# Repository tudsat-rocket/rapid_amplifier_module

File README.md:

# FRoDo Amplifier Module
this module is meant to be a general-purpose amplifier which is going to be used for all analogue sensors which will be in the rocket, those include the WIKA pressure sensors as well as the fancy-fins strain gauges.

## Description
The main function of the module is to amplify signals with low voltage levels that are too small to be useful for our ADCs. Therefore the board has two sides with solder pads, one to connect to the IO board and one to connect to a sensor. The layout is designed in a way, that the sensor side is compatible with the WIKA TPR-Flex PCBs.

## Features
* Selectable gain (1-1000) -> the selection of RG1 will determine the gain (G = 1 + 49,4kOhm/RG)
* selectable offset -> output offset can either be 0V or Vcc/2
* Breakaway mounting holes
## Connections
### To IO-Board:
Connects the amplifier module with the IO-Board with the following pins:
* u+  ->  positive supply voltage (3-36V)
* u-  ->  gnd as "neg" supply voltage (only use in single supply mode) | reference for the output signal.
* o+  ->  amplified signal, references gnd (u-)
* ref  ->  selected reference signal (0V or Vcc/2) can be used to get additional information (e.g. detect noise on supply line(?))

### To sensor:
Connects the amplifier module with the Sensor with the following pins:
* u+  -> positive supply voltage (filtered supply voltage)
* u-  -> neg. supply voltage (gnd)
* s+  -> positive signal
* s-  -> negative signal

## User guideline:
The Gain resistor (RG1) must be chosen in a way that the expected maximum amplified voltage is lower than 4.85V (5V - 0.15V) and the expected minimum amplified voltage is higher than 0.1V if a smaller (or negative) output voltage is expected the solder jumper for the reference voltage needs to be connected to 3 to set an output shift.
Only if the connected sensor is expected to output a signal which exclusively results in an output signal that is in the above given values, can the reference solder jumper be set to 1.

The above-given adjustments are necessary as the IO module is only able to read values between 0V and 5V. A higher Input voltage can be used if the connected sensor needs a supply voltage which exceeds 5V. The amplified signal then still needs to be smaller than the given 4.85V.

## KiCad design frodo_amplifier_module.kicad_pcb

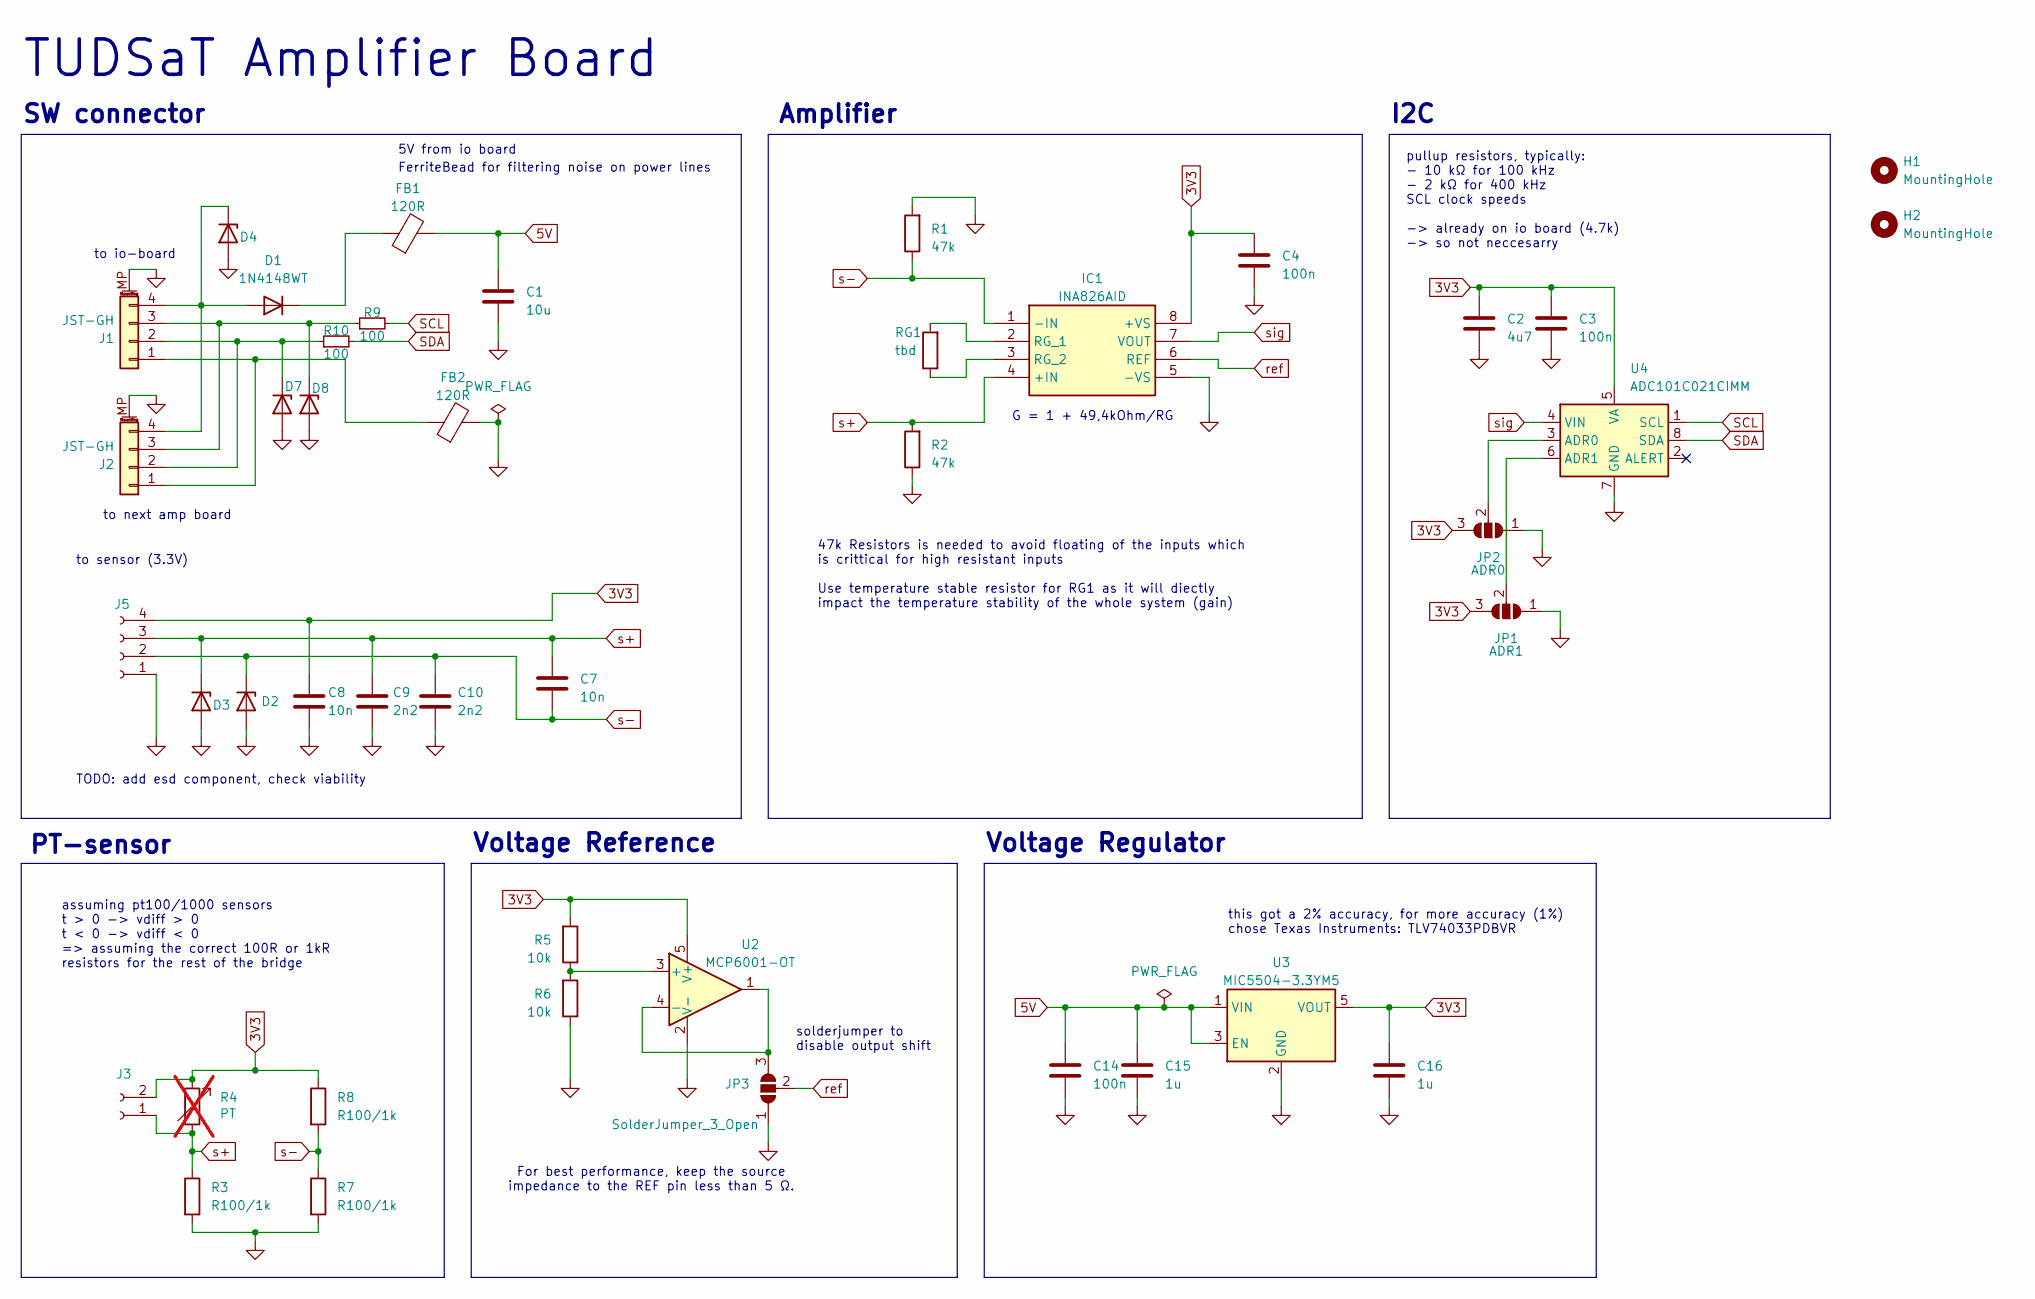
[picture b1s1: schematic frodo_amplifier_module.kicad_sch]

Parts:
C1: 10u; C_0402_1005Metric; LCSC C315248
C2: 4u7; C_0402_1005Metric; LCSC C23733
C3, C4, C14: 100n; C_0402_1005Metric; LCSC C1525
C7, C8: 10n; C_0402_1005Metric; LCSC C15195
C9, C10: 2n2; C_0402_1005Metric; LCSC C84703
C15, C16: 1u; C_0402_1005Metric; LCSC C76999
D1: 1N4148WT; D_SOD-523
D2, D3, D4, D7, D8: ESD5Zxx; D_SOD-523
FB1, FB2: 120R; L_0402_1005Metric; LCSC C76891
H1, H2: MountingHole; MountingHole_2.2mm_M2_DIN965_Pad
IC1: INA826AID; WSON-8-1EP_3x3mm_P0.5mm_EP1.2x2mm; Mouser Part Number 595-INA826AID
J1, J2: JST-GH; JST_GH_SM04B-GHS-TB_1x04-1MP_P1.25mm_Horizontal; Part# BM04B-GHS-TBT; LCSC C161692
J3: Conn_01x02_Socket; R_Axial_DIN0204_L3.6mm_D1.6mm_P1.90mm_Vertical
J5: Conn_01x04_Socket; PinHeader_1x04_P1.27mm_Vertical
JP1: ADR1; SolderJumper-3_P1.3mm_Open_RoundedPad1.0x1.5mm
JP2: ADR0; SolderJumper-3_P1.3mm_Open_RoundedPad1.0x1.5mm
JP3: SolderJumper_3_Open; SolderJumper-3_P1.3mm_Open_Pad1.0x1.5mm
R1: 47k; R_0402_1005Metric; LCSC C25792
R2: 47k; R_0402_1005Metric_Pad0.72x0.64mm_HandSolder; LCSC C25792
R3, R7, R8: R100/1k; R_0805_2012Metric_Pad1.20x1.40mm_HandSolder
R4: PT; not fitted
R5, R6: 10k; R_0402_1005Metric_Pad0.72x0.64mm_HandSolder; LCSC C25744
R9, R10: 100; R_0402_1005Metric; Part# RC0402FR-07100RL; LCSC# C106232
RG1: tbd; R_1206_3216Metric_Pad1.30x1.75mm_HandSolder
U2: MCP6001-OT; SOT-23-5; LCSC C116490
U3: MIC5504-3.3YM5; SOT-23-5; LCSC C3021093
U4: ADC101C021CIMM; MSOP-8_3x3mm_P0.65mm; LCSC C1543337

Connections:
3V3: C2.1, C3.1, C4.1, C8.1, C16.1, IC1.8 (+VS), J3.2, J5.4, JP1.3 (B), JP2.3 (B), R4.1, R5.2, R8.1, U2.5 (V+), U3.5 (VOUT), U4.5 (VA)
5V: C1.1, C14.1, C15.1, FB1.2, U3.1 (VIN), U3.3 (EN)
GND: C1.2, C2.2, C3.2, C4.2, C8.2, C9.2, C10.2, C14.2, C15.2, C16.2, D2.2 (A), D3.2 (A), D4.2 (A), D7.2 (A), D8.2 (A), FB2.2, IC1.5 (-VS), J1.MP (MountPin), J2.MP (MountPin), J5.1, JP1.1 (A), JP2.1 (A), JP3.1 (A), R1.2, R2.1, R3.2, R6.1, R7.2, U2.2 (V-), U3.2 (GND), U4.7 (GND)
unnamed: D1.2 (A), D4.1 (K), J1.4, J2.4
unnamed: D1.1 (K), FB1.1
unnamed: D7.1 (K), J1.2, J2.2, R10.1
unnamed: D8.1 (K), J1.3, J2.3, R9.1
unnamed: IC1.2 (RG_1), RG1.2
unnamed: IC1.3 (RG_2), RG1.1
unnamed: FB2.1, J1.1, J2.1
unnamed: JP1.2 (C), U4.6 (ADR1)
unnamed: JP2.2 (C), U4.3 (ADR0)
unnamed: JP3.3 (B), U2.1, U2.4 (-)
unnamed: R5.1, R6.2, U2.3 (+)
SCL: R9.2, U4.1 (SCL)
SDA: R10.2, U4.8 (SDA)
ref: IC1.6 (REF), JP3.2 (C)
s+: C7.1, C9.1, D3.1 (K), IC1.4 (+IN), J3.1, J5.3, R2.2, R3.1, R4.2
s-: C7.2, C10.1, D2.1 (K), IC1.1 (-IN), J5.2, R1.1, R7.1, R8.2
sig: IC1.7 (VOUT), U4.4 (VIN)

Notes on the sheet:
pullup resistors, typically: - 10 kΩ for 100 kHz - 2 kΩ for 400 kHz SCL clock speeds -> already on io board (4.7k) -> so not neccesarry
to sensor (3.3V)
G = 1 + 49,4kOhm/RG
SW connector
Voltage Regulator
to next amp board
TODO: add esd component, check viability
5V from io board
FerriteBead for filtering noise on power lines
solderjumper to disable output shift
TUDSaT Amplifier Board
Voltage Reference
47k Resistors is needed to avoid floating of the inputs which is crittical for high resistant inputs Use temperature stable resistor for RG1 as it will diectly impact the temperature stability of the whole system (gain)
I2C
assuming pt100/1000 sensors t > 0 -> vdiff > 0 t < 0 -> vdiff < 0 => assuming the correct 100R or 1kR resistors for the rest of the bridge
Amplifier
PT-sensor
this got a 2% accuracy, for more accuracy (1%) chose Texas Instruments: TLV74033PDBVR
to io-board
For best performance, keep the source impedance to the REF pin less than 5 Ω.

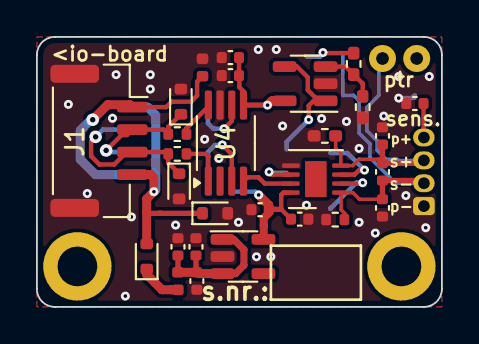
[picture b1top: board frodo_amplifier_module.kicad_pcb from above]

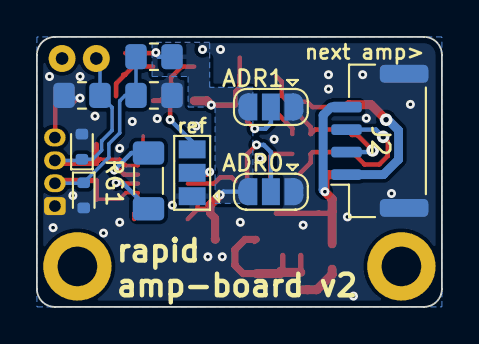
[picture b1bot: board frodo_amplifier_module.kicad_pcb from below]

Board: 4 copper layers, 22.5 x 15.0 mm, 42 parts (10 on the bottom side), 20 nets.

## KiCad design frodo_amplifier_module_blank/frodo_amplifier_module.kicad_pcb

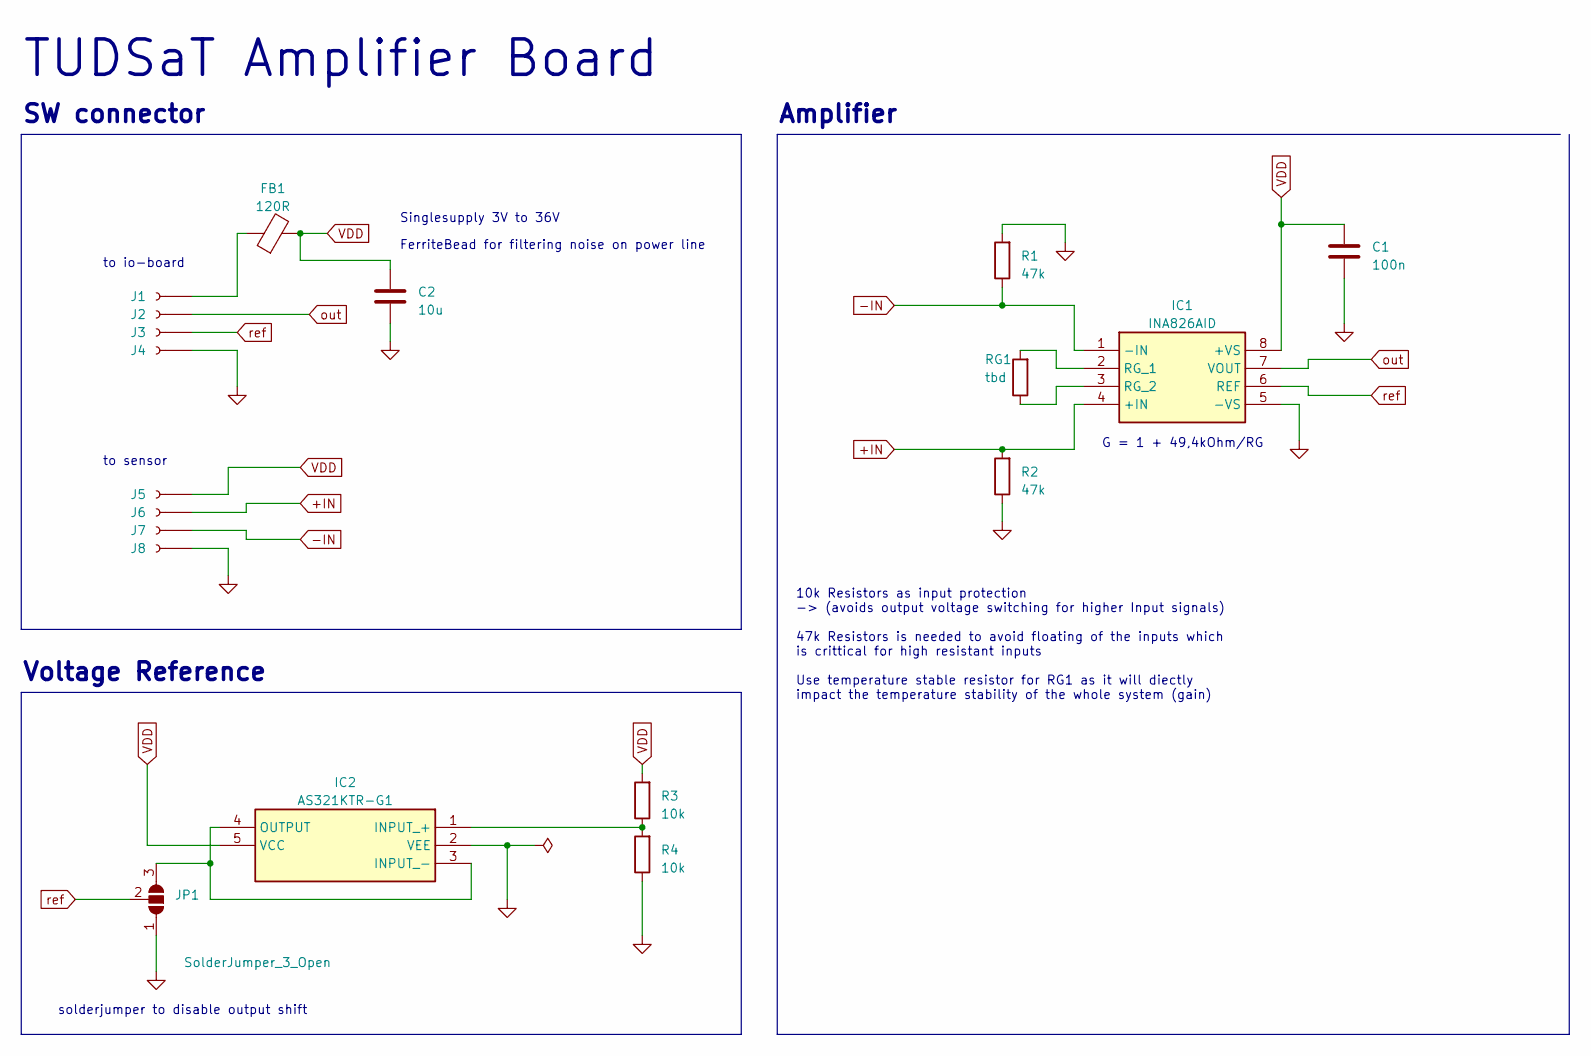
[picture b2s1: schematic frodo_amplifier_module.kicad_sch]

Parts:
C1: 100n; C_0402_1005Metric_Pad0.74x0.62mm_HandSolder
C2: 10u; C_0603_1608Metric
FB1: 120R; L_0603_1608Metric
IC1: INA826AID; SOIC-8_3.9x4.9mm_P1.27mm; Mouser Part Number 595-INA826AID
IC2: AS321KTR-G1; SOT-23-5; Mouser Part Number 621-AS321KTR-G1
J1, J2, J3, J4, J5, J6, J7, J8: Conn_01x01_Socket; SolderWirePad_1x01_SMD_1x2mm
JP1: SolderJumper_3_Open; SolderJumper-3_P1.3mm_Open_RoundedPad1.0x1.5mm_NumberLabels
R1, R2: 47k; R_0402_1005Metric_Pad0.72x0.64mm_HandSolder
R3, R4: 10k; R_0402_1005Metric_Pad0.72x0.64mm_HandSolder
RG1: tbd; R_0603_1608Metric_Pad0.98x0.95mm_HandSolder

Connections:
+IN: IC1.4 (+IN), J6.1, R2.2
-IN: IC1.1 (-IN), J7.1, R1.1
GND: C1.2, C2.2, IC1.5 (-VS), IC2.2 (VEE), J4.1, J8.1, JP1.1 (A), R1.2, R2.1, R4.1
unnamed: IC1.2 (RG_1), RG1.2
unnamed: IC1.3 (RG_2), RG1.1
unnamed: IC2.1 (INPUT_+), R3.1, R4.2
unnamed: IC2.3 (INPUT_-), IC2.4 (OUTPUT), JP1.3 (B)
unnamed: FB1.1, J1.1
VDD: C1.1, C2.1, FB1.2, IC1.8 (+VS), IC2.5 (VCC), J5.1, R3.2
out: IC1.7 (VOUT), J2.1
ref: IC1.6 (REF), J3.1, JP1.2 (C)

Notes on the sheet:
to sensor
G = 1 + 49,4kOhm/RG
SW connector
Singlesupply 3V to 36V
FerriteBead for filtering noise on power line
TUDSaT Amplifier Board
Voltage Reference
10k Resistors as input protection -> (avoids output voltage switching for higher Input signals) 47k Resistors is needed to avoid floating of the inputs which is crittical for high resistant inputs Use temperature stable resistor for RG1 as it will diectly impact the temperature stability of the who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
Amplifier
solderjumper to disable output shift
to io-board

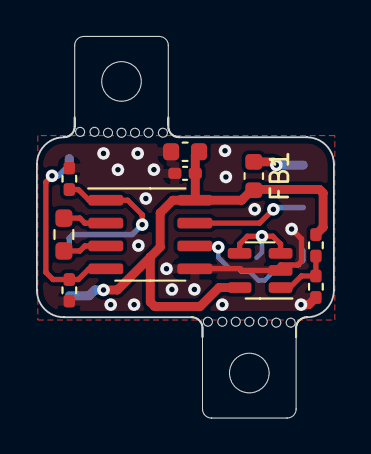
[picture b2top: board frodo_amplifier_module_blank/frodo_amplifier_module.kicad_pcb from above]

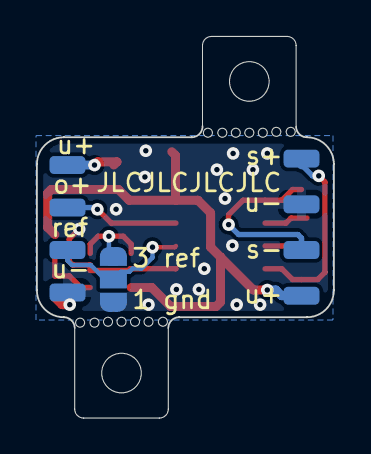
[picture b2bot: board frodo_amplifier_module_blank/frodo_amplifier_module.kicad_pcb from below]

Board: 2 copper layers, 16.5 x 21.2 mm, 21 parts (9 on the bottom side), 11 nets.

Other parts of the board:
mouse-bite-2mm-slot, mouse-bite-2mm-slot#2: VAL**; mouse-bite-2mm-slot

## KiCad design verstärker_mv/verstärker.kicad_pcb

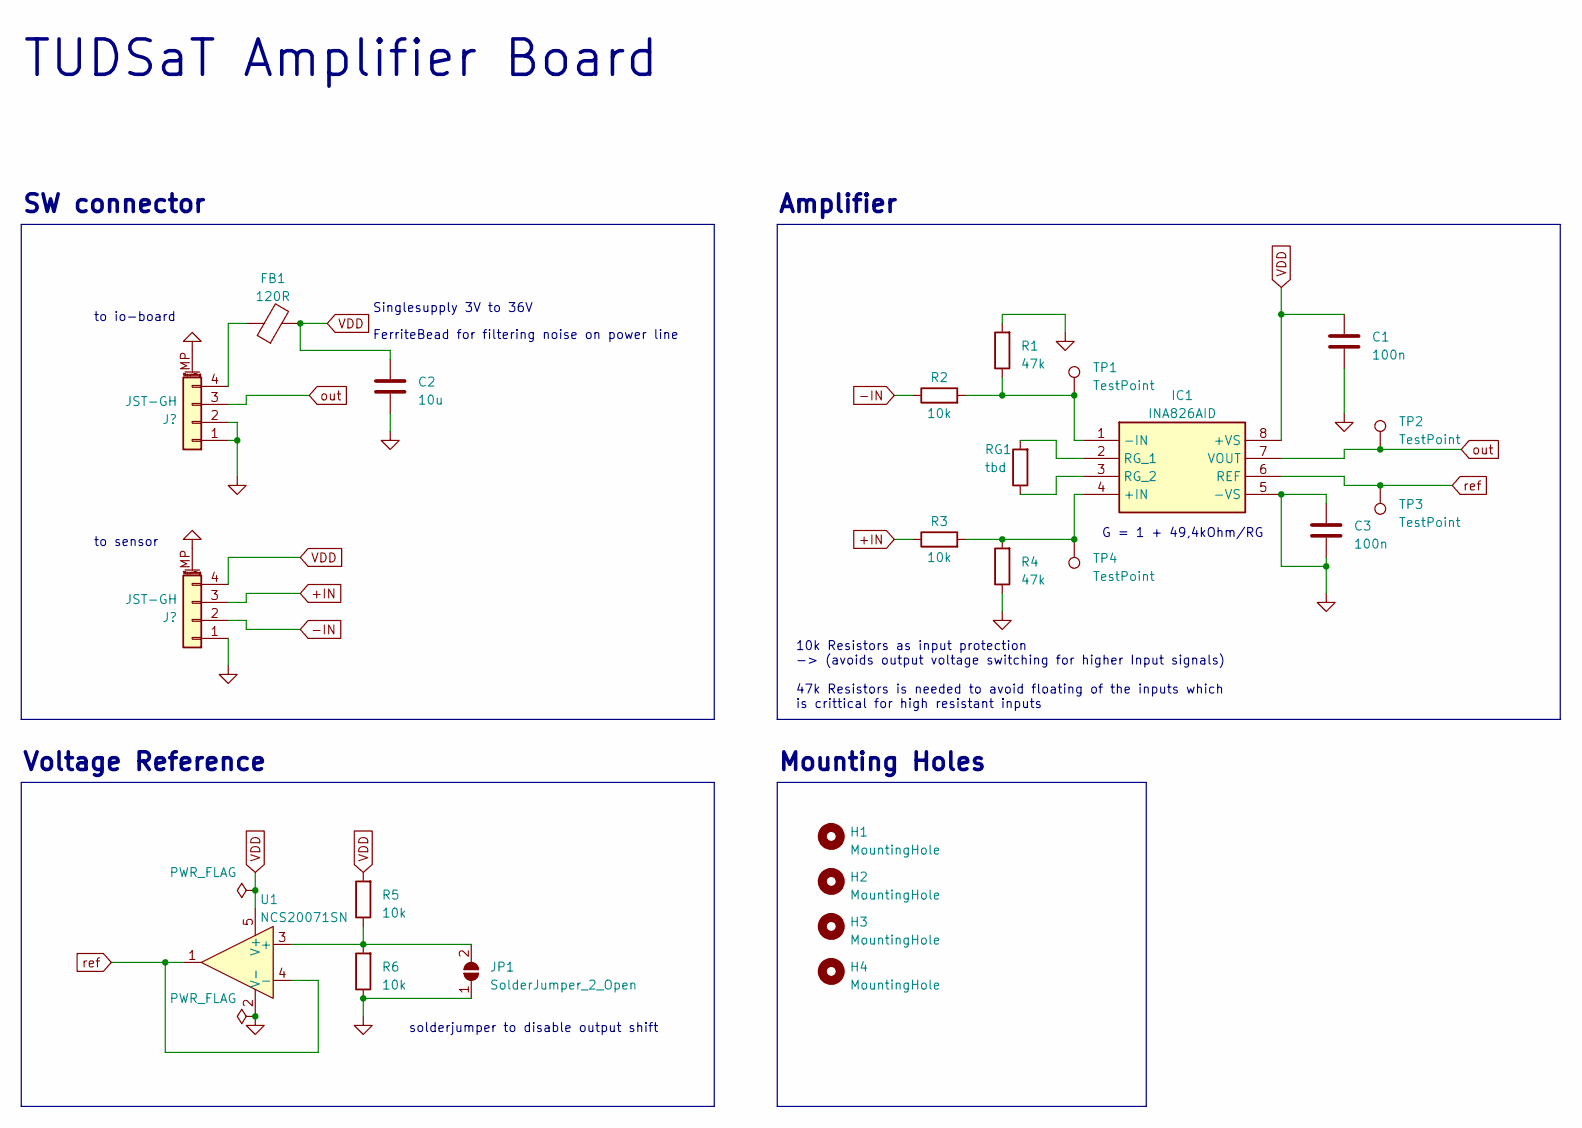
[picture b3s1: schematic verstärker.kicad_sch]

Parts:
C1, C3: 100n; C_0402_1005Metric_Pad0.74x0.62mm_HandSolder
C2: 10u; C_0402_1005Metric_Pad0.74x0.62mm_HandSolder
FB1: 120R; L_0402_1005Metric_Pad0.77x0.64mm_HandSolder
H1, H2, H3, H4: MountingHole; MountingHole_2.2mm_M2_ISO7380_Pad
IC1: INA826AID; SOIC-8_3.9x4.9mm_P1.27mm; Mouser Part Number 595-INA826AID
J1, J2: JST-GH; JST_GH_SM04B-GHS-TB_1x04-1MP_P1.25mm_Horizontal; Part# BM04B-GHS-TBT; LCSC# C161692
JP1: SolderJumper_2_Open; SolderJumper-2_P1.3mm_Open_Pad1.0x1.5mm
R1, R4: 47k; R_0402_1005Metric_Pad0.72x0.64mm_HandSolder
R2, R3, R5, R6: 10k; R_0402_1005Metric_Pad0.72x0.64mm_HandSolder
RG1: tbd; R_0603_1608Metric_Pad0.98x0.95mm_HandSolder
TP1, TP2, TP3, TP4: TestPoint; TestPoint_Pad_D1.5mm
U1: NCS20071SN; TSOP-5_1.65x3.05mm_P0.95mm

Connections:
+IN: J2.3, R3.1
-IN: J2.2, R2.1
GND: C1.2, C2.2, C3.1, C3.2, IC1.5 (-VS), J1.1, J1.2, J1.MP (MountPin), J2.1, J2.MP (MountPin), JP1.1 (A), R1.2, R4.1, R6.1, U1.2 (V-)
unnamed: IC1.4 (+IN), R3.2, R4.2, TP4.1
unnamed: IC1.1 (-IN), R1.1, R2.2, TP1.1
unnamed: IC1.2 (RG_1), RG1.2
unnamed: IC1.3 (RG_2), RG1.1
unnamed: FB1.1, J1.4
unnamed: JP1.2 (B), R5.1, R6.2, U1.3 (+)
VDD: C1.1, C2.1, FB1.2, IC1.8 (+VS), J2.4, R5.2, U1.5 (V+)
out: IC1.7 (VOUT), J1.3, TP2.1
ref: IC1.6 (REF), TP3.1, U1.1, U1.4 (-)

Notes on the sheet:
to sensor
G = 1 + 49,4kOhm/RG
SW connector
Mounting Holes
Singlesupply 3V to 36V
FerriteBead for filtering noise on power line
TUDSaT Amplifier Board
Voltage Reference
10k Resistors as input protection -> (avoids output voltage switching for higher Input signals) 47k Resistors is needed to avoid floating of the inputs which is crittical for high resistant inputs
Amplifier
solderjumper to disable output shift
to io-board

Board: 2 copper layers, 24 parts (0 on the bottom side), 12 nets, no tracks yet.

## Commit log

2024-01-09 Add files via upload
    sry Jesko, bekomm es grad nicht besser hin wir können da ma zusammen drüberschauen dass des mit den namen etc. alles passt.
2024-01-10 file structure cleanup
2024-01-16 updated amplifier module, removed mounting holes and routed the pcb
2024-01-18 updated stuff
2024-01-18 added stuff
2024-01-20 fixed soulder jumper, added mousbites
2024-01-21 fixed my messup
2024-01-24 updated mounting holes and footprints of c2 and fb1
2024-01-25 changed mounting holes
2024-01-29 changed folder layout, optimised gnd routing
2024-01-29 Create README.md
    added general description of the amp module and how to use it properly
2024-01-29 added silcscrean for better usability
2024-01-29 added silcscreen
2024-01-29 Update README.md
    only small grammar update
2024-02-27 added kicad files
2024-02-27 started adding wika recomendations
2024-03-25 continued working on v0.2
2024-03-26 implemented wikas recomendations to scematic
2024-04-07 finished the scematics
2024-04-07 started the pcb layout for the amp module
2024-04-14 finished pcb layout - routing not done yet
2024-04-20 finished routing -> pcb should be ready to order after review
2024-05-20 optimised via placement
2024-07-04 fixed silkscreen
2024-07-04 remove 3v3ref, merge fills, adjust layout, fill BOM
2026-02-03 finished amp module rev3
2026-02-12 fixed design errors in amp board
2026-02-16 did kicad design checks and adjusted design accordingly
